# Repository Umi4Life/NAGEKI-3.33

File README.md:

# NAGEKI 3.33
A full size Ongeki controller

# General Requirements
 - Access to 3d printer and good 3d printing knowledge
 - Soldering tool
 - x4~5 filaments, the brand I used is eSUN PLA+
 - 22~26 AWG wires
 - Crimping tool
 - Access to laser cutter & poster printer & sticker printer
 - Some CAD knowledge
 - Some Arduino coding knowledge
 - Ability to DIY stuff up if things doesn't go your way

# Additional resources
-  [Rhythm Cons Wiki](https://rhythm-cons.wiki/w/Main_Page)
-  [Cons&Stuff Discord](https://discord.com/invite/fknwz8s) - ping me @Zekamashi#7734 if you're struggling; some resources required are also pinned in `#ongeki` channel in this server

# Table of Contents
1. [Lever](#lever)
2. [WAD](#wad)
3. [Case](#case)
4. [Graphics](#graphics)
5. [Buttons and PCB](#buttons-and-pcb)
6. [Firmwares](#firmwares)

## Lever
### Toxikmango
#### Parts required
| Part                                                                     | Qty |
|--------------------------------------------------------------------------|-----|
| Everything listed in https://github.com/toxikmango/Ongeki-Lever*         |     |
| x2 M8 or 5/16" threaded bolts(75mm) and nuts                             | 2   |
| silicone tube for threaded bolts, OD ~12                                 | 2   |
  - *PandAuto pot can be substituted for cheap potentiometer, the one I used is B10k
  - *Fully threaded bolts can be either hex bolt or studded

#### Print settings
15-20% infill, 2 infill line multiplier, 3 wall line count, 0.20-0.28mm layer height

#### Assembly
1. Print out the `base with stoppers.stl` from `/LEVER/toximango/` in this repo. Lever assembly for studded bolt is straightforward, just thread it into `lever.stl` from the original repo.
If you're using hex threaded bolt then print out the `lever big.stl` and `long nut.stl` instead. Then thread long nut into the end of the bolt, wrap some teflon tape around it and jam it into the `lever big.stl`.
Might want to add nylock and a nut on where the bottom of the knob would go, but don't put on the knob itself yet, we will do it after mounting everything into the case.

2. Mount potentiometer into the base. If your pot have a "tooth" on it then use soldering iron to melt down small hole into the base to have it lay flat on the surface.
Use a socket wrench to help tighten it in place

3. Print out the rest of the parts from original repo

4. Now for the shaft assembly, start by inserting the tension chuck, 2 nuts (one goes into the bottom the chuck, another just to position the bearing) and bearing into the threaded bolt
    - Sanding tension chuck down to 1000 grit is also recommended

5. Check that the chuck lines up with the clamp    

Add nylock and another nut

Insert the end of the bolt into the base, then add lever, nylock, nut and bearing in respectively   
The order right now should be:    
[Hex bolt]---[Nut]---[Nut]---[Bearing]---[Nylock]---[Nut]---[Lever]---[Nylock]---[Nut]---[Bearing]--->

Start torquing everything into place.    
Spur gear for the potentiometer should be added around this point. If your pot shaft is star-shaped then use ` Spur Gear (12 teeth) knurled.stl` from this repo instead.

6. Stop torquing when the lever stays on the exact center of the base. Tightens the nut at the back of the lever into it.    
It's highly recommended to cover the end of the shaft with a washer and a nylock too, to lock it in place and keep it from slipping off
7. Add both clamps into the assembly. Again, you might want to sand the clamp surface down for smoother lever.
### Abi
Files are pinned in `#ongeki` channel in Cons&Stuff server    
I did not use this lever design on my controller because the parts are too difficult to source, 
but I did upload my own f3d design for coil coupler so that it would fit in controller case, and you can mess 
with the setting to have its diameter match your coil. 

## WAD
### Parts required
| Part                                                                                 | Qty |
|--------------------------------------------------------------------------------------|-----|
| 100g button springs (the same ones used on main/sdvx buttons)                        | 2   |
| M3 flange nut                                                                        | 2   |
| M3 spring washer                                                                     | 2   |
| M4x20~25mm screws                                                                    | 3   |
| M4 flange nut                                                                        | 3   |
| IR Optocoupler + breakout board (the sensor mount I made is designed to fit ITR9608) | 1   |
| WS2812b + something to mount the cables on                                           | 6   |

### Print settings
- 10% infill, 1 infill line multiplier, 2 wall line count, 0.20 layer height for button face (
  - print it vertically using tree support
  - make it as light as possible
  - I haven't tried this yet but printing in clear PETG will give better light pass through and might give better feel
- 12% infill, 1 infill line multiplier, 3 wall line count, 0.20 layer height for the rest
  - might need to do spitting if you're using 200mm bed like ender3

### Assembly
Wire up and mount everything as shown in picture below. If your sensor is not ITR9608 or has different dimension then you might want to model up a
different 30x20mm mount.    
I made mount models with different heights to test out button sensitivity. The one I find most accurate is 6mm mount. 
Feel free to experiment with these heights but according to many source, the button should feel the same as maimai button which is VERY sensitive and activates by just wiggling.    
You can also add some keyboard tape/thin foam on where the button would make contact with the shield for longevity.

## Case
### Parts required
| Part                        | Qty |
|-----------------------------|-----|
| M5*20 mm screws             | 12  |
| M5 nut                      | 12  |
| M4*20 mm countersunk screws | ~30 |
| M3*20 mm countersunk screws | ~16 |
| M3*10 mm screws             | ~16 |
| M3*5 mm countersunk screws  | 24  |
| M3 Nut/ flange nut          | ~16 |
| M3 Nut                      | 24  |
| Epoxy glue                  | 80g |
| Cabinet magnet              | 10  |
| Big rubber adhesive feet    | ~8  |
### Print settings
- 12% infill, 1 infill line multiplier, 3 wall line count, 0.28 layer height
  - support may be needed on some part

### Assembly
1. Glue up each side parts with epoxy glue, don't forget to sand down with 80 grit sandpaper before applying glue to make the bond stronger. 
Get the bottom part laser cut with 2mm acrylic instead if you want to save sanity.    
2. You should now have 7 big parts; top, wad(left), wad(right), side(north), side(south), bottom. 
Everything except bottom part can be screwed together with self threading hole. Then mount cabinet magnet onto the bottom part.     
3. Loosely mount side button and run cable down into the hole. Glue M5 nut on the WAD cover hole and mount it over side button. 
Make sure the side button backplate doesn't get caught in between and start tightening the screws    
4. Mount lever assembly under the case then insert the knob. Use teflon tape to make the knob tight-fit and start smacking it into place 
(hold the bottom of the lever while doing so, be careful damaging/breaking the top side!). 
Make sure that the countersunk screws is flush with the surface to prepare for acrylic cover.

### Notes
- I also include .dxf files for each side in case you want to get MDF cut instead (not tested)
- Epoxy glue smells awful. Do this either outdoor or in a well ventilated room

## Graphics
| Part                    | Qty |
|-------------------------|-----|
| M5x20 Round flat screws | 6   |
| M5 flange Nut           | 6   |
### Assembly
#### Acrylic cover:   
- Laser cut with 4mm clear acrylic

#### Cover graphic:
- Print it with printing service of your choice, for mine, I ink-jetted it on PP paper
- Put your acrylic over on top of it and use a pen to trace all the holes
- Cut every hole out with a knife
- Neardayo's Faucetwo customization video to get a better picture: https://www.youtube.com/watch?v=mpwCRY_63XE
- Put the printed paper on top of your case, cover it with acrylic and screw it down. Do not tighten it too hard or the acrylic will crack

#### WAD Decal:
- Print it on vinyl sticker (I went to an Itasha shop to get mine)
- Before applying sticker don't forget to sand the surface where it would go down to 1000 grit

### Notes
- You may notice that the top of cover & graphic is 1cm shorter than the case. This is because lots of shop I went to check can only print 30cm wide. 
Feel free to add 1 cm to the top if your printing service is capable of wider print
- For top cover you can do reverse UV print instead if you want to go extra
- Once the cover is mounted onto the case you may find the WAD cover impossible to remove without having to take the cover off first. 
You can get around by sliding left/right to access side button screws to remove the side button first, then the WAD cover

## Buttons and PCB
### Parts required
| Part                         | Qty |
|------------------------------|-----|
| 60*60 mm square buttons\*    | 6   |
| 33*33 mm square buttons      | 2   |
| 4.8mm female spade connector | 16  |
| WS2812b                      | 6   |
| Arduino Pro Micro            | 1   |
| 6 pin JST XH                 | 8   |
| 4 pin JST XH                 | 4   |
| 3 pin JST XH                 | 1   |
| 2 pin JST XH                 | 2   |
| M3x10mm screws               | 4   |
- *if you're using Sanwa make sure lamp holder is the old style

### Assembly
[Use this](https://www.thingiverse.com/thing:2204192) to mount WS2812b to your 60*60 buttons, use teflon tape to make everything fit snugly. 
Order the pcb from [JLCPCB](https://jlcpcb.com/) or any pcb printing service of your choice.
Route connect the first WS2812b DIN to A1 and DOUT to L1OUT, then connect the next WS2812b DIN to L1OUT and DOUT to L2OUT etc. etc.    
Slide the PCB to 3d printed enclosure, secure it with screws and use double side tape to mount it under the case.

## Firmwares
There are 3 firmwares that I recommend
- [skogaby/OngekiCon.ino](https://gist.github.com/skogaby/59331321ba9427996ff1c941a32b05f4) - uses XInput, needs to short RST pin to GND pin everytime you want to re-upload code
- [ongeki-io](https://github.com/Nana0Nana/ongeki-io) - has hid lighting, looks fancy on song selection
- [mouse&keyboard](https://github.com/Nana0Nana/NAGEKI/blob/main/nageki2.0%20code/nageki2.0.ino) - use this if you want to play MuDrive

For all of these code I suggest you include `ResponsiveAnalogRead` library to get smoother lever reading.
```
...
#include <ResponsiveAnalogRead.h>
ResponsiveAnalogRead analog({{LEVER_PIN}}, true);
...
```

Make sure the code follows PCB's pin in/out    

| Component              | Pin |
|------------------------|-----|
| Left button 1          | 9   |
| Left button 2          | 8   |
| Left button 3          | 7   |
| Right button 1         | 6   |
| Right button 2         | 5   |
| Right button 3         | 4   |
| Left Menu              | 15  |
| Right Menu             | 10  |
| Lever                  | A0  |
| Main buttons LEDs      | A1  |
| Left side button LEDs  | A2  |
| Right side button LEDs | A3  |

Your photo interrupter's breakout board may have unobstructed=HIGH configuration.
In this case you will need to invert side buttons' logic.

# Closing Notes
- To test how well it plays (especially the wads), try エータ・ベータ・イータ on master difficulty
- Main buttons spacing are 1mm off from official spec. You are inhuman if you notice the difference between this and official panel
- Do not use this controller to stream "that" on GDQ

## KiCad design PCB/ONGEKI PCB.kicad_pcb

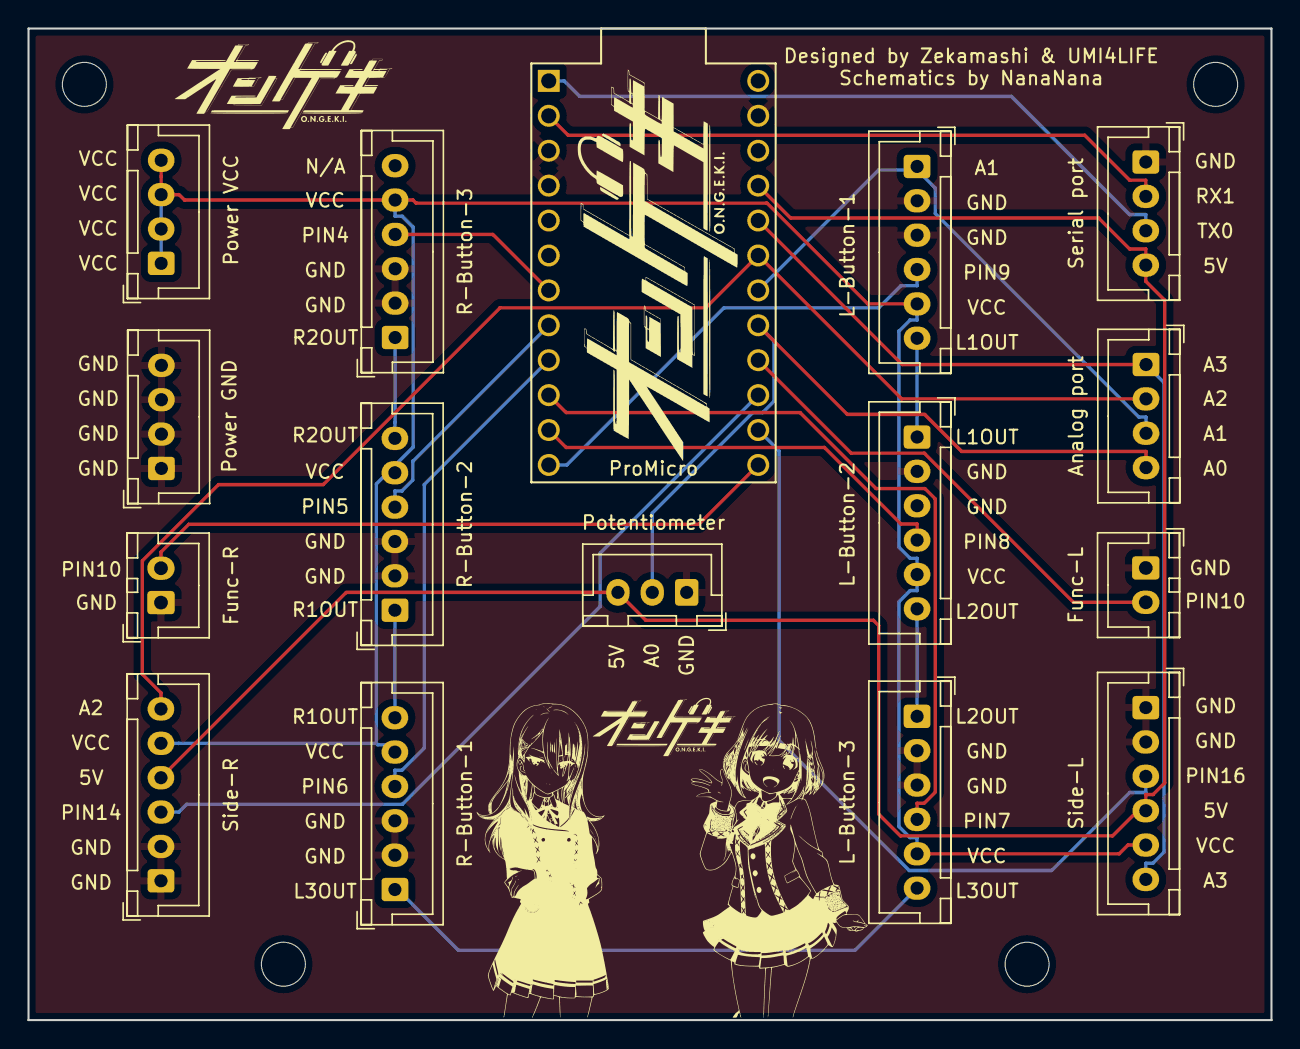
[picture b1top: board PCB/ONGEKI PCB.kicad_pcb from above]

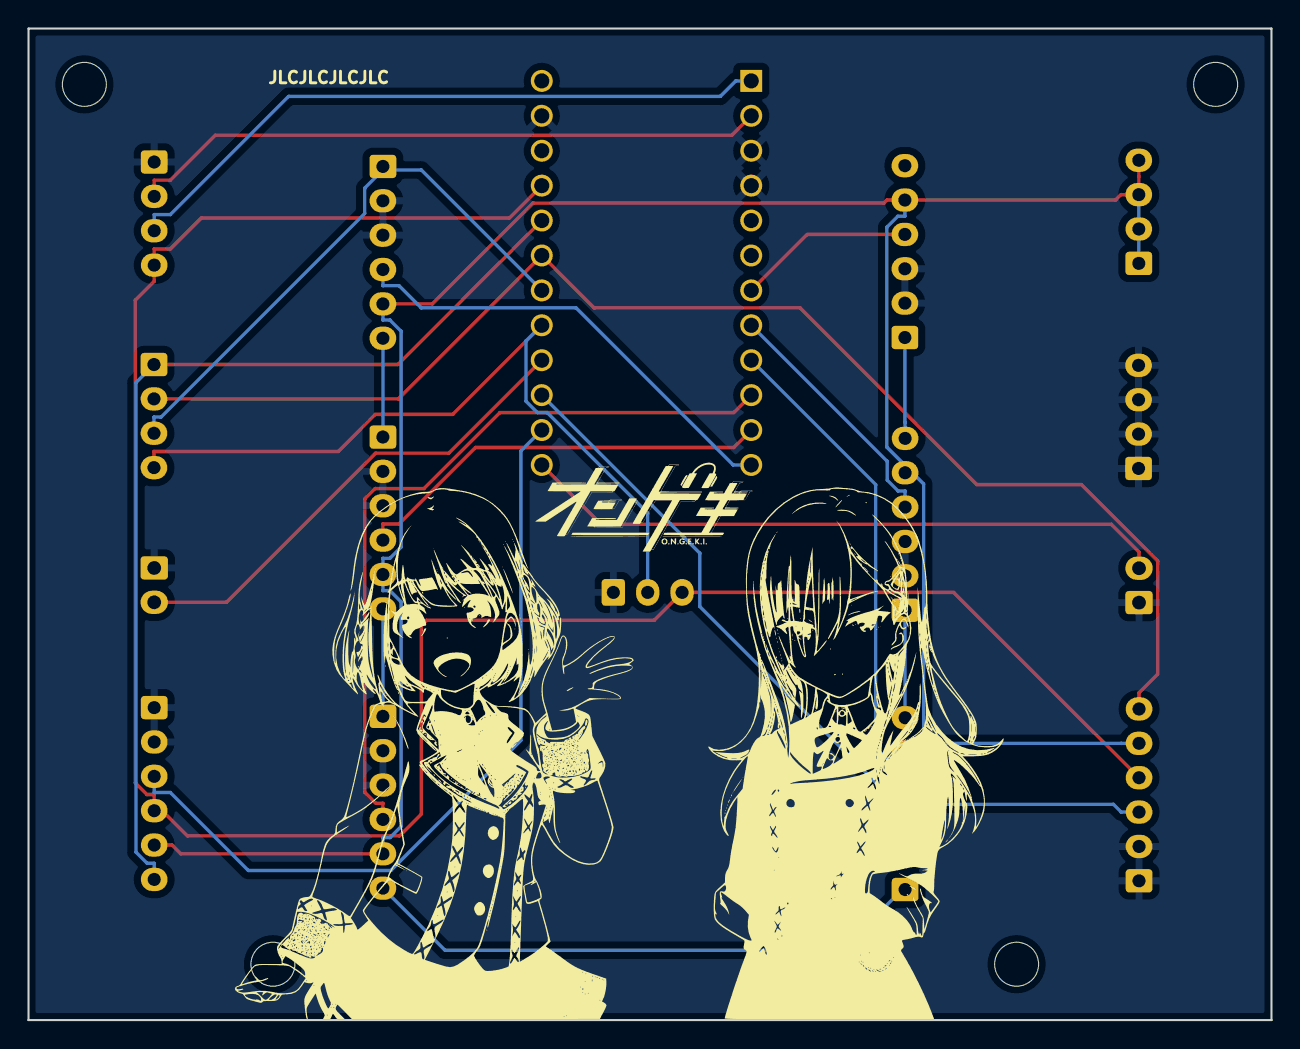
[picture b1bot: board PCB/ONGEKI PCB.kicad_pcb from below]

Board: 2 copper layers, 90.4 x 72.1 mm, 27 parts (3 on the bottom side), 24 nets.

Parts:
Analog port: Analog port; JST_XH_B4B-XH-A_1x04_P2.50mm_Vertical
Func-L: Func-L; JST_XH_B2B-XH-A_1x02_P2.50mm_Vertical
Func-R: Func-R; JST_XH_B2B-XH-A_1x02_P2.50mm_Vertical
L-Button-1: L-Button-1; JST_XH_B6B-XH-A_1x06_P2.50mm_Vertical
L-Button-2: L-Button-2; JST_XH_B6B-XH-A_1x06_P2.50mm_Vertical
L-Button-3: L-Button-3; JST_XH_B6B-XH-A_1x06_P2.50mm_Vertical
Potentiometer: Potentiometer; JST_XH_B3B-XH-A_1x03_P2.50mm_Vertical
Power GND: Power GND; JST_XH_B4B-XH-A_1x04_P2.50mm_Vertical
Power VCC: Power VCC; JST_XH_B4B-XH-A_1x04_P2.50mm_Vertical
ProMicro: ProMicro; ProMicro-EnforcedTop
R-Button-1: R-Button-1; JST_XH_B6B-XH-A_1x06_P2.50mm_Vertical
R-Button-2: R-Button-2; JST_XH_B6B-XH-A_1x06_P2.50mm_Vertical
R-Button-3: R-Button-3; JST_XH_B6B-XH-A_1x06_P2.50mm_Vertical
REF1**, REF2**, REF4**, REF5**: MountingHole_3.2mm_M3
Serial port: Serial port; JST_XH_B4B-XH-A_1x04_P2.50mm_Vertical
Side-L: Side-L; JST_XH_B6B-XH-A_1x06_P2.50mm_Vertical
Side-R: Side-R; JST_XH_B6B-XH-A_1x06_P2.50mm_Vertical
akari-back: LOGO
akari-front: LOGO
ongeki-back: LOGO
ongeki-front-lg: LOGO
ongeki-front-sm: LOGO
setsuba-back: LOGO
setsuna-front: LOGO

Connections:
5V: Potentiometer.3, ProMicro.5V, Serial port.4, Side-L.4, Side-R.4
A0: Analog port.4, Potentiometer.2, ProMicro.A0
A1: Analog port.3, L-Button-1.1, ProMicro.A1
A2: Analog port.2, ProMicro.A2, Side-R.6
A3: Analog port.1, ProMicro.A3, Side-L.6
EX_VCC: L-Button-1.5, L-Button-2.5, L-Button-3.5, Power VCC.1, Power VCC.2, Power VCC.3, Power VCC.4, R-Button-1.5, R-Button-2.5, R-Button-3.5, Side-L.5, Side-R.5
GND: Func-L.1, Func-R.1, L-Button-1.2, L-Button-1.3, L-Button-2.2, L-Button-2.3, L-Button-3.2, L-Button-3.3, Potentiometer.gn, Power GND.1, Power GND.2, Power GND.3, Power GND.4, ProMicro.GND, R-Button-1.2, R-Button-1.3, R-Button-2.2, R-Button-2.3, R-Button-3.2, R-Button-3.3, Serial port.1, Side-L.1, Side-L.2, Side-R.1, Side-R.2
L1OUT: L-Button-1.6, L-Button-2.1
L2OUT: L-Button-2.6, L-Button-3.1
L3OUT: L-Button-3.6, R-Button-1.L3OUT
PIN4: ProMicro.4, R-Button-3.4
PIN5: ProMicro.5, R-Button-2.4
PIN6: ProMicro.6, R-Button-1.4
PIN7: L-Button-3.4, ProMicro.7
PIN8: L-Button-2.4, ProMicro.PIN8
PIN9: L-Button-1.4, ProMicro.9
PIN10: Func-R.2, ProMicro.10
PIN14: ProMicro.14, Side-R.3
PIN15: Func-L.2, ProMicro.15
PIN16: ProMicro.16, Side-L.3
R1OUT: R-Button-1.6, R-Button-2.1
R2OUT: R-Button-2.6, R-Button-3.1
RX1: ProMicro.RX1, Serial port.2
TX0: ProMicro.TX0, Serial port.3

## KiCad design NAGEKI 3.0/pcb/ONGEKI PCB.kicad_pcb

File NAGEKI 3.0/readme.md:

# Render by OCTANE4.0

# Befor you Build this controller,I recommend you have CAD Fundamentals and redraw screw holes.

# New UV pattern 

# New Lever handle Design by myself

# New PCB Design by myself

## For design reasons, only SVG images of schematics is posted.

# Lever Damping Design

## For somereason, The Design of Lever Damping Will not posted But you can Build it by your self.

### pictures:

Official:

Nageki:

confidential :)

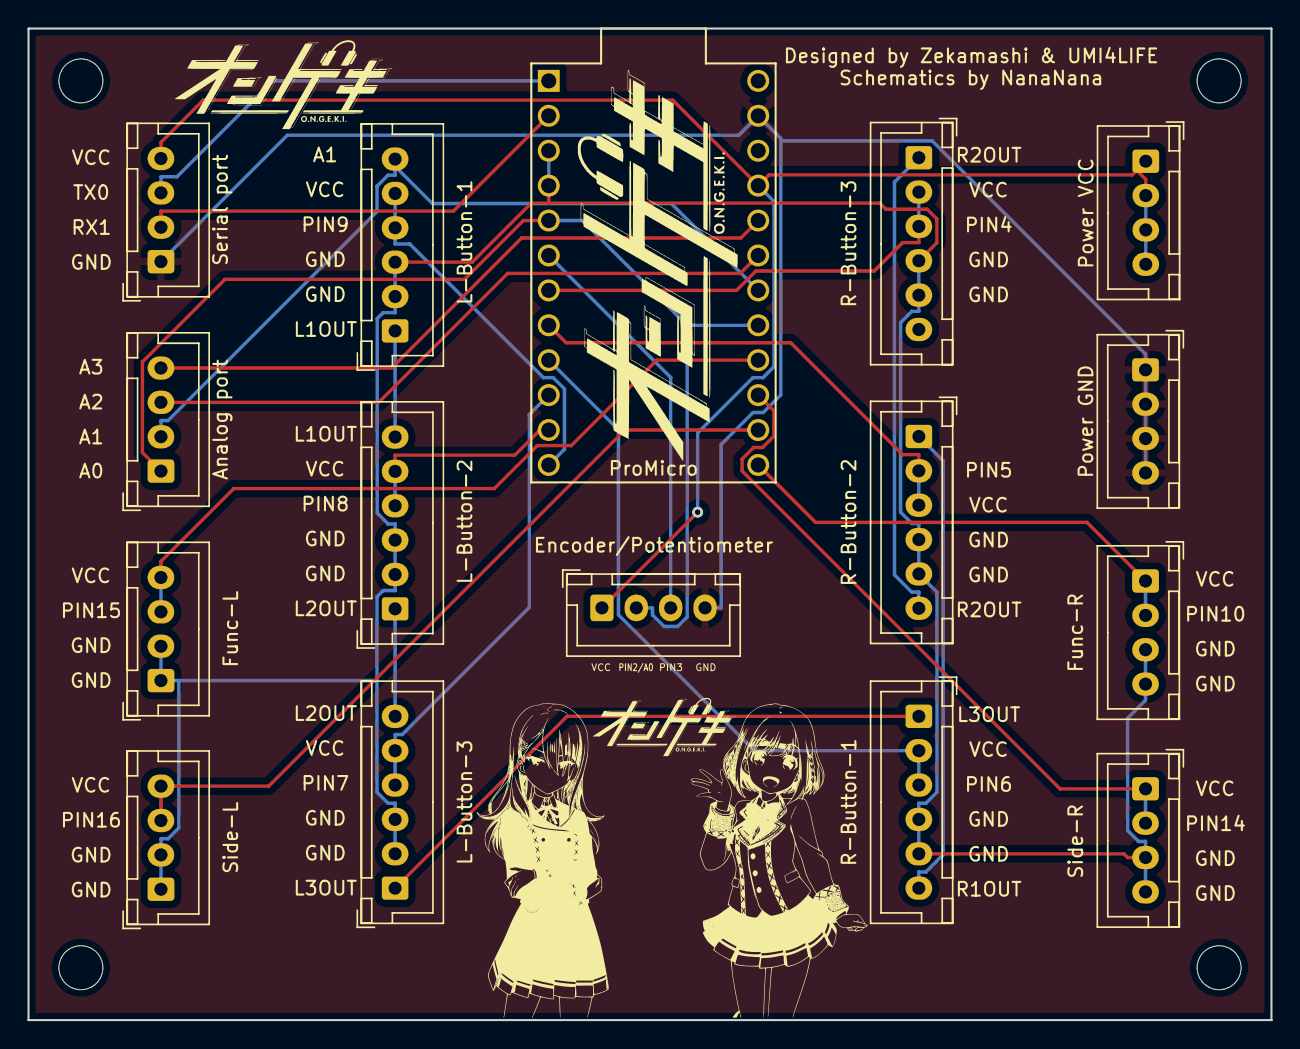
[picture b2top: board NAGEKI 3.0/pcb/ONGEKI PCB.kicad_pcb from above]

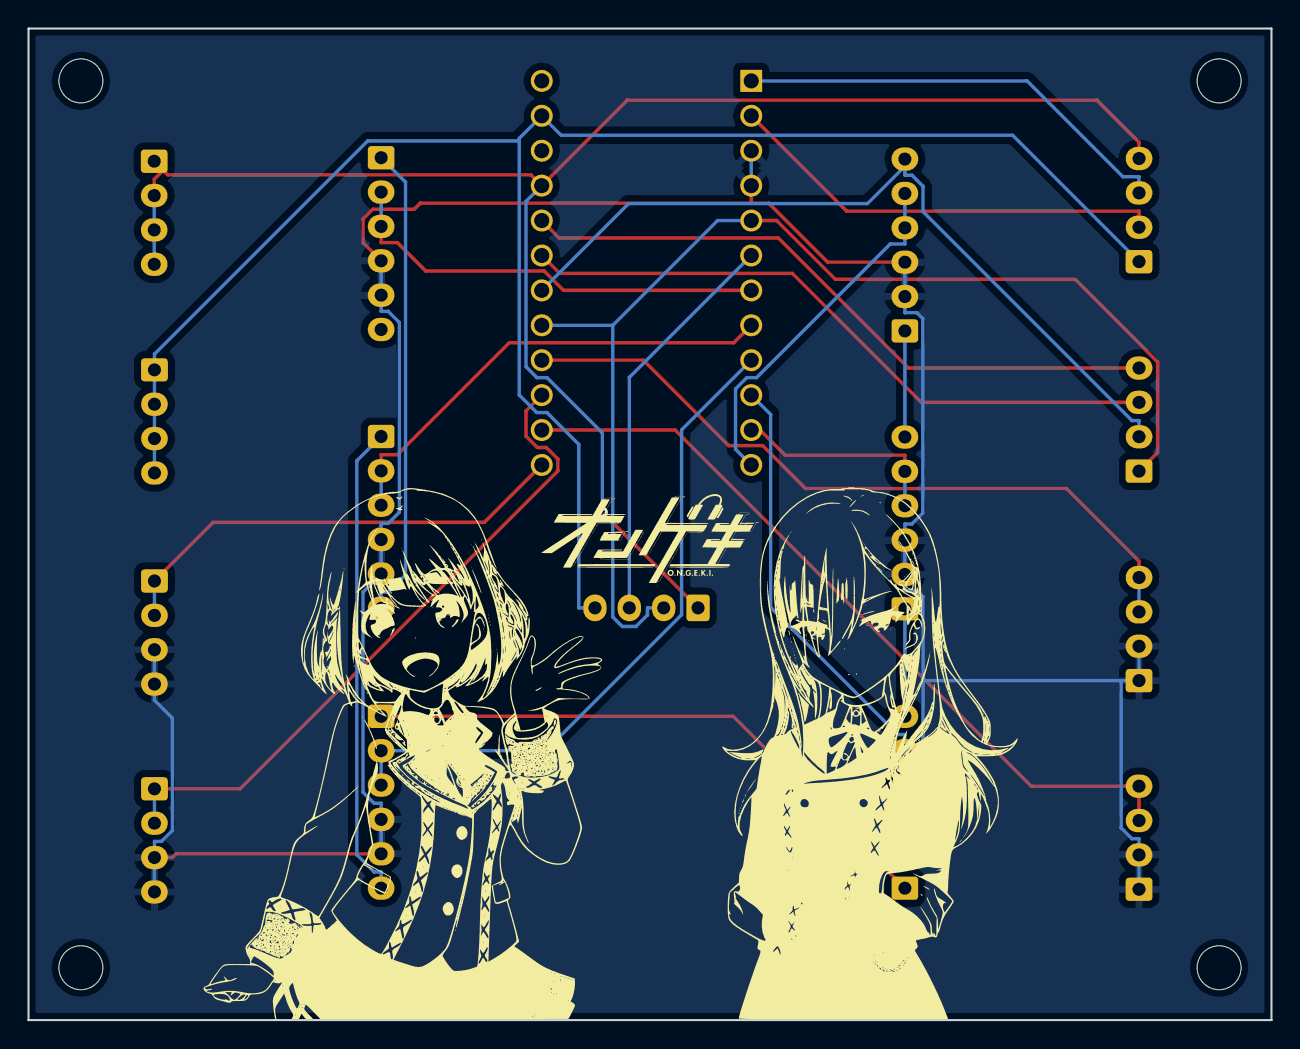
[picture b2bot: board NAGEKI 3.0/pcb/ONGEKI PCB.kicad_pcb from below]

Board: 2 copper layers, 90.4 x 72.1 mm, 27 parts (3 on the bottom side), 25 nets.

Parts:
Analog port: Analog port; JST_XH_B4B-XH-A_1x04_P2.50mm_Vertical
Encoder/Potentiometer: Encoder/Potentiometer; JST_XH_B4B-XH-A_1x04_P2.50mm_Vertical
Func-L: Func-L; JST_XH_B4B-XH-A_1x04_P2.50mm_Vertical
Func-R: Func-R; JST_XH_B4B-XH-A_1x04_P2.50mm_Vertical
L-Button-1: L-Button-1; JST_XH_B6B-XH-A_1x06_P2.50mm_Vertical
L-Button-2: L-Button-2; JST_XH_B6B-XH-A_1x06_P2.50mm_Vertical
L-Button-3: L-Button-3; JST_XH_B6B-XH-A_1x06_P2.50mm_Vertical
Power GND: Power GND; JST_XH_B4B-XH-A_1x04_P2.50mm_Vertical
Power VCC: Power VCC; JST_XH_B4B-XH-A_1x04_P2.50mm_Vertical
ProMicro: ProMicro; ProMicro-EnforcedTop
R-Button-1: R-Button-1; JST_XH_B6B-XH-A_1x06_P2.50mm_Vertical
R-Button-2: R-Button-2; JST_XH_B6B-XH-A_1x06_P2.50mm_Vertical
R-Button-3: R-Button-3; JST_XH_B6B-XH-A_1x06_P2.50mm_Vertical
REF1**, REF2**, REF4**, REF5**: MountingHole_3.2mm_M3
Serial port: Serial port; JST_XH_B4B-XH-A_1x04_P2.50mm_Vertical
Side-L: Side-L; JST_XH_B4B-XH-A_1x04_P2.50mm_Vertical
Side-R: Side-R; JST_XH_B4B-XH-A_1x04_P2.50mm_Vertical
akari-back: LOGO
akari-front: LOGO
ongeki-back: LOGO
ongeki-front-lg: LOGO
ongeki-front-sm: LOGO
setsuba-back: LOGO
setsuna-front: LOGO

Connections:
A1: Analog port.2, L-Button-1.6, ProMicro.A1
A2: Analog port.3, ProMicro.A2
A3: Analog port.4, ProMicro.A3
GND1: Func-L.1, Func-L.2, Func-R.3, Func-R.4, L-Button-1.2, L-Button-1.3, L-Button-2.2, L-Button-2.3, L-Button-3.2, L-Button-3.3, ProMicro.GND, ProMicro.GND1, R-Button-1.4, R-Button-1.5, R-Button-2.4, R-Button-2.5, R-Button-3.4, R-Button-3.5, Side-L.1, Side-L.2, Side-R.3, Side-R.4
GND2: Encoder/Potentiometer.4, Power GND.1, Power GND.2, Power GND.3, Power GND.4, ProMicro.GND, Serial port.1
L1OUT: L-Button-1.1, L-Button-2.6
L2OUT: L-Button-2.1, L-Button-3.6
L3OUT: L-Button-3.1, R-Button-1.1
PIN2/17: Analog port.1, Encoder/Potentiometer.2, ProMicro.2, ProMicro.A0
PIN3: Encoder/Potentiometer.3, ProMicro.3
PIN4: ProMicro.4, R-Button-3.2, R-Button-3.3
PIN5: ProMicro.5, R-Button-2.2, R-Button-2.3
PIN6: ProMicro.6, R-Button-1.2, R-Button-1.3
PIN7: L-Button-3.4, L-Button-3.5, ProMicro.7
PIN8: L-Button-2.4, L-Button-2.5, ProMicro.PIN8
PIN9: L-Button-1.4, L-Button-1.5, ProMicro.9
PIN10: Func-R.1, Func-R.2, ProMicro.10
PIN14: ProMicro.14, Side-R.1, Side-R.2
PIN15: Func-L.3, Func-L.4, ProMicro.15
PIN16: ProMicro.16, Side-L.3, Side-L.4
R1OUT: R-Button-1.6, R-Button-2.1
R2OUT: R-Button-2.6, R-Button-3.1
RX1: ProMicro.RX1, Serial port.2
TX0: ProMicro.TX0, Serial port.3
VCC: Encoder/Potentiometer.1, Power VCC.1, Power VCC.2, Power VCC.3, Power VCC.4, ProMicro.VCC, Serial port.4

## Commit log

2021-10-21 New PCB design by Cubic
    thanks so much!
2021-10-21 PCB 2.0 DESIGN BY CUBIC
2021-10-27 PCB file
2021-10-27 DONT USE
2021-10-28 CODE for new PCB
2021-10-28 Add files via upload
    ADD English
2021-10-28 this for ongeki-io
    https://github.com/GEEKiDoS/ongeki-io
2021-10-28 V1 PCB
2021-10-28 V1 PCB
    OLD PCB
2021-10-28 V2 PCB
    NEW PCB
2021-10-28 SIDE PCB
2021-11-24 new skins for surface
2021-11-24 NEW UV PRINT SURFACE
2021-12-09 Nageki2.0 code
    hold two menu button to swip card(hold enter)
2021-12-09 2.0 surface fix
    fix button
2021-12-09 Nageki 2.0
    fix
2021-12-09 UV painting
2022-05-05 Create LICENSE
    Even is using Mozilla Public License
    BUT COMMERCIAL USE WAS NOT ALLOWED
2022-05-05 4.0 PCB
    add 6keys lights
2022-05-10 3D render pic
2022-06-08 side button?
2022-06-08 #3.0
2022-06-08 PCB Schematic
2022-06-08 Rename readme to readme.md
2022-06-08 confidential
2022-08-31 3d printed case
2022-10-10 cleanup & upload the rest of resources
    update readme
2022-10-15 update readme
    formatting
    add more stuff
    add more stuff 2
    add more stuff 3
    add more stuff 4
2022-10-16 Update README.md
    add more stuff 5
